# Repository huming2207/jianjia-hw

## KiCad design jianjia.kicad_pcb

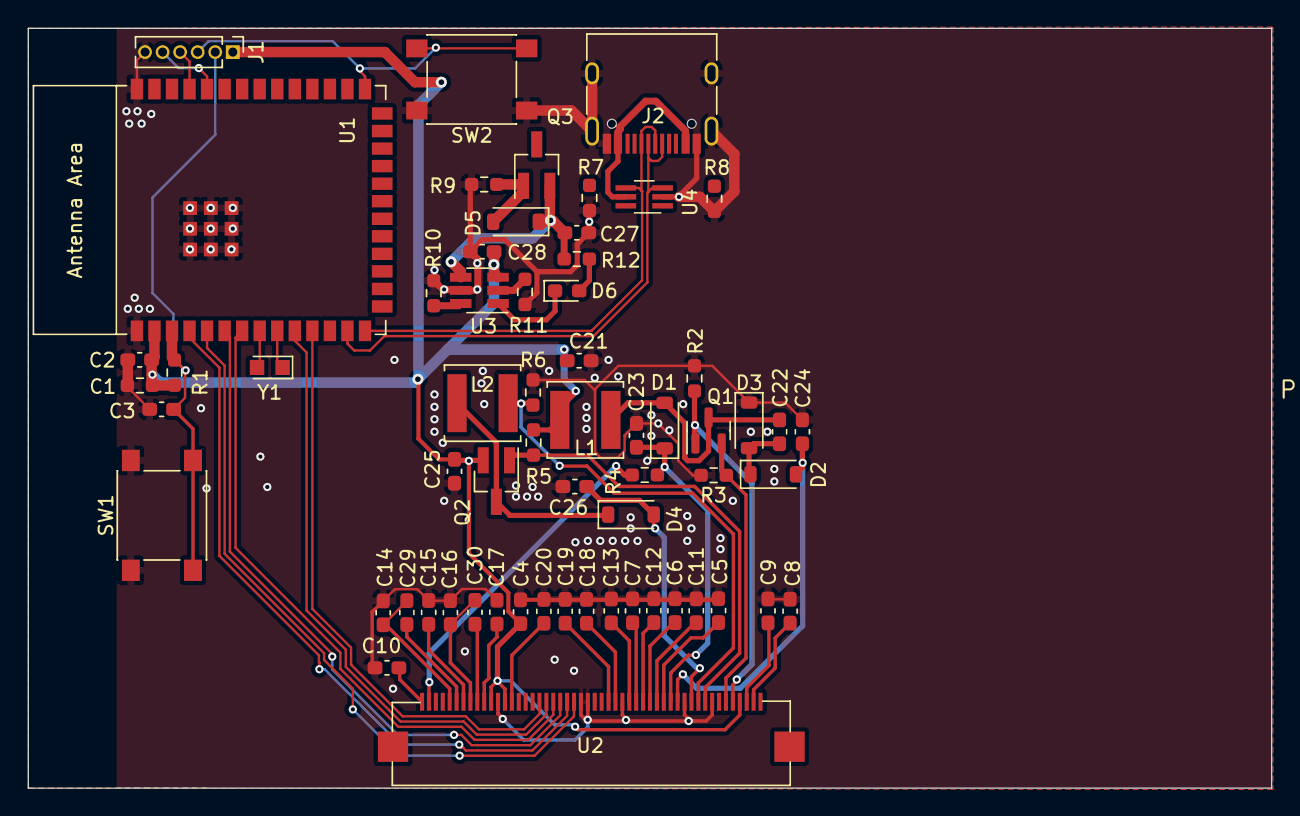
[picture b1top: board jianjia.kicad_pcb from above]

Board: 2 copper layers, 90.0 x 55.0 mm, 62 parts (0 on the bottom side), 53 nets.

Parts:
C1: 10uF/25v; R_0603_1608Metric_Pad0.98x0.95mm_HandSolder
C2, C4: 100nF; C_0603_1608Metric_Pad1.08x0.95mm_HandSolder
C3, C14, C15, C16, C17, C18, C19, C27, C28, C29, C30: 1uF/10v; C_0603_1608Metric_Pad1.08x0.95mm_HandSolder
C5, C6, C7, C11, C12, C13, C22, C23, C24, C26: 10uF/25v; C_0603_1608Metric_Pad1.08x0.95mm_HandSolder
C8, C21, C25: 4.7uF/10v; C_0603_1608Metric_Pad1.08x0.95mm_HandSolder
C9, C10: 0.47uF/25v; C_0603_1608Metric_Pad1.08x0.95mm_HandSolder
C20: 2.2uF/6.3v; C_0603_1608Metric_Pad1.08x0.95mm_HandSolder
D1, D2, D3, D4, D5: MBR0530; D_SOD-123
D6: LED; LED_0603_1608Metric_Pad1.05x0.95mm_HandSolder
J1: PROG; PinHeader_1x06_P1.27mm_Vertical
J2: USB; USB_C_Receptacle_HRO_TYPE-C-31-M-12
L1, L2: NRS5020T150MMGJ; L_Sunlord_SWPA5020S
Q1: BSS138; SOT-23
Q2, Q3: SI2301CDS; SOT-23_Handsoldering
R1: 10k; R_0603_1608Metric_Pad0.98x0.95mm_HandSolder
R2, R5: 1M; R_0603_1608Metric_Pad0.98x0.95mm_HandSolder
R3, R6: 0.47R; R_0603_1608Metric_Pad0.98x0.95mm_HandSolder
R4: 0R; R_0603_1608Metric_Pad0.98x0.95mm_HandSolder
R7, R8: 5.11k; R_0603_1608Metric_Pad0.98x0.95mm_HandSolder
R9: 1k; R_0603_1608Metric_Pad0.98x0.95mm_HandSolder
R10: 4.7k; R_0603_1608Metric_Pad0.98x0.95mm_HandSolder
R11: 62k; R_0603_1608Metric_Pad0.98x0.95mm_HandSolder
R12: 150R; R_0603_1608Metric_Pad0.98x0.95mm_HandSolder
SW1: RESET; SW_Push_1P1T_NO_6x6mm_H9.5mm
SW2: BOOT/CONFIG; SW_Push_1P1T_NO_6x6mm_H9.5mm
U1: ESP32-S3-WROOM-2
U2: AC073TC1_FH34SRJ-50S-0.5SH
U3: CN3130; SOT-23-6_Handsoldering
U4: CH412K; SOT-363_SC-70-6_Handsoldering
Y1: 32.768k; Crystal_SMD_2012-2Pin_2.0x1.2mm_HandSoldering

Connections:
+5V: D5.2 (A), J2.A4 (VBUS), J2.A9 (VBUS), J2.B4 (VBUS), J2.B9 (VBUS), Q3.1 (G), R9.1, U4.5 (VCC)
+BATT: C1.1, C2.1, C4.1, C21.2, C25.1, C28.1, J1.1, L1.1, Q2.2 (S), R1.1, R5.1, U1.2 (3V3), U2.4 (VDD), U2.38 (VDD), U2.40 (VDDIO), U3.3 (BAT)
BOOT: J1.3, SW2.2, U1.27 (GPIO0/BOOT)
CHG_VIN: C27.1, D5.1 (K), Q3.2 (S), R12.1, U3.4 (VIN)
CP1N: C29.1, U2.45 (CP1N)
CP1P: C14.1, C29.2, U2.46 (CP1P)
CP2N: C30.1, U2.42 (CP2N)
CP2P: C16.1, C30.2, U2.43 (CP2P)
DBG_RXD: J1.5, U1.36 (U0RXD/GPIO44/CLK_OUT2)
DBG_TXD: J1.4, U1.37 (U0TXD/GPIO43/CLK_OUT1)
DISP_BUSY: U1.4 (GPIO4/TOUCH4/ADC1_CH3), U2.29 (BUSY_N)
DISP_CS: U1.7 (GPIO7/TOUCH7/ADC1_CH6), U2.31 (CS#)
DISP_DATA: U1.11 (GPIO18/U1RXD/ADC2_CH7/CLK_OUT3), U2.33 (SI0)
DISP_DC: U1.6 (GPIO6/TOUCH6/ADC1_CH5), U2.30 (DC#)
DISP_RST: U1.5 (GPIO5/TOUCH5/ADC1_CH4), U2.28 (RES#)
DISP_SCLK: U1.10 (GPIO17/U1TXD/ADC2_CH6), U2.32 (SCL)
EN: C3.1, J1.2, R1.2, SW1.2, U1.3 (EN)
FPL_VCOM: C9.1, U2.3 (FPL_VCOM)
GDRC: Q2.1 (G), R5.2, U2.9 (GDRC)
GDRH: Q1.1 (G), R2.1, U2.5 (GDRH)
GND: C1.2, C2.2, C3.2, C4.2, C5.2, C6.2, C7.2, C8.2, C9.2, C10.2, C11.2, C12.2, C13.2, C14.2, C15.2, C16.2, C17.2, C18.2, C19.2, C20.2, C21.1, C23.2, C24.2, C25.2, C26.2, C27.2, C28.2, D3.1 (K), J1.6, J2.A1 (GND), J2.A12 (GND), J2.B1 (GND), J2.B12 (GND), J2.S1 (SHIELD), R2.2, R3.2, R6.1, R7.2, R8.2, R9.2, R10.2, R11.2, SW1.1, SW2.1, U1.1 (GND), U1.40 (GND), U1.41 (GND), U2.8 (GND), U2.12 (GND), U2.21 (GNDA), U2.26 (BS0), U2.27 (BS1), U2.39 (GND), U3.5 (GND), U4.2 (GND)
unnamed: C22.1, D1.2 (A), L1.2, Q1.3 (D)
unnamed: C22.2, D2.1 (K), D3.2 (A)
unnamed: D4.1 (K), L2.1, Q2.3 (D)
unnamed: D6.2 (A), R12.2
unnamed: D6.1 (K), U3.1 (nCHG)
unnamed: J2.A5 (CC1), R8.1
unnamed: J2.B5 (CC2), R7.1
unnamed: U1.8 (GPIO15/U0RTS/ADC2_CH4/XTAL_32K_P), Y1.2
unnamed: U1.9 (GPIO16/U0CTS/ADC2_CH5/XTAL_32K_N), Y1.1
unnamed: R11.1, U3.2 (FB)
unnamed: R10.1, U3.6 (ISET)
REFN: C19.1, U2.23 (REFN)
REFP: C18.1, U2.22 (REFP)
RESEC: L2.2, R6.2, U2.10 (RESEC)
RESEH: Q1.2 (S), R3.1, U2.6 (RESEH)
TFT_VCOM: C8.1, U2.2 (TFT_VCOM)
USB_DM: J2.A7 (D-), J2.B7 (D-), U1.13 (GPIO19/U1RTS/ADC2_CH8/CLK_OUT2/USB_D-), U4.3 (IO2)
USB_DP: J2.A6 (D+), J2.B6 (D+), U1.14 (GPIO20/U1CTS/ADC2_CH9/CLK_OUT1/USB_D+), U4.4 (IO3)
VCOMBD: C10.1, U2.50 (VCOMBD)
VCP1: C15.1, U2.44 (VCP1)
VCP2: C17.1, U2.41 (VCP2)
VDDO: C20.1, U2.37 (VDDO)
VGH: R4.2, U2.49 (VGH)
VGL: C24.1, D2.2 (A), U2.13 (VGL)
VPC: C26.1, D4.2 (A), U2.11 (VPC)
VPH: C23.1, D1.1 (K), R4.1, U2.14 (VPH)
VSH: C5.1, U2.15 (VSH)
VSH_LV: C11.1, U2.16 (VSH_LV)
VSH_LV2: C6.1, U2.17 (VSH_LV2)
VSL: C12.1, U2.18 (VSL)
VSL_LV: C7.1, U2.19 (VSL_LV)
VSL_LV2: C13.1, U2.20 (VSL_LV2)

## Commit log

2023-05-18 Init
2023-05-19 Init schematic
2023-05-19 Add gitignore
2023-05-19 Add ESP KiCad library
2023-06-09 Rev 1: initial schematic
2023-06-11 Rev 1.0: finalise schematic
2023-06-11 Sync lib
2023-07-12 Exclude lock file
2023-07-12 Rev 1: refine layout, typo fixes
2023-07-13 rev1: tune PCB
